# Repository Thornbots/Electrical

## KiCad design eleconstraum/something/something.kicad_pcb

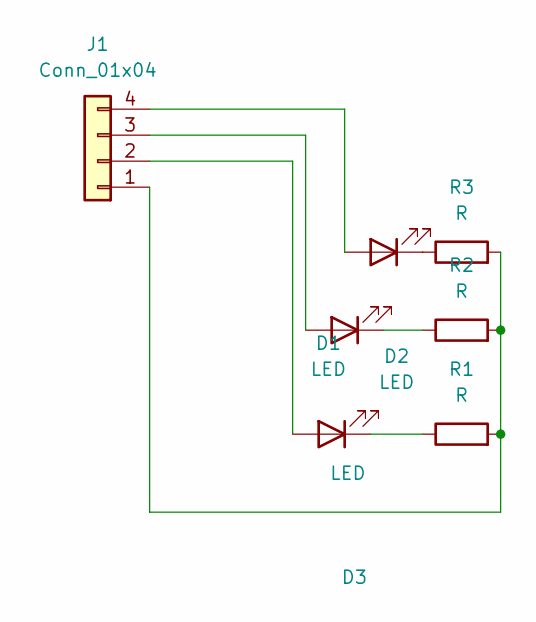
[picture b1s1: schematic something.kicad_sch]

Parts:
D1, D2, D3: LED
J1: Conn_01x04
R1, R2, R3: R

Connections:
unnamed: D1.2 (A), J1.4
unnamed: D1.1 (K), R3.1
unnamed: D2.2 (A), J1.3
unnamed: D2.1 (K), R2.1
unnamed: D3.2 (A), J1.2
unnamed: D3.1 (K), R1.1
unnamed: J1.1, R1.2, R2.2, R3.2

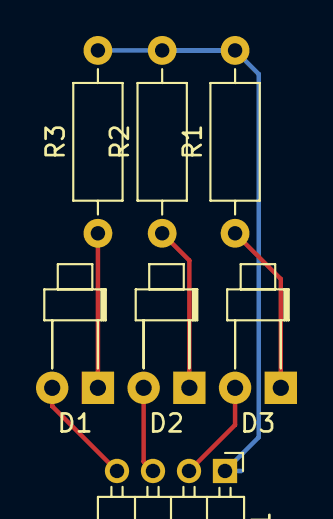
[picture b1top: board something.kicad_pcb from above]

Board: 2 copper layers, 7 parts (0 on the bottom side), 7 nets.

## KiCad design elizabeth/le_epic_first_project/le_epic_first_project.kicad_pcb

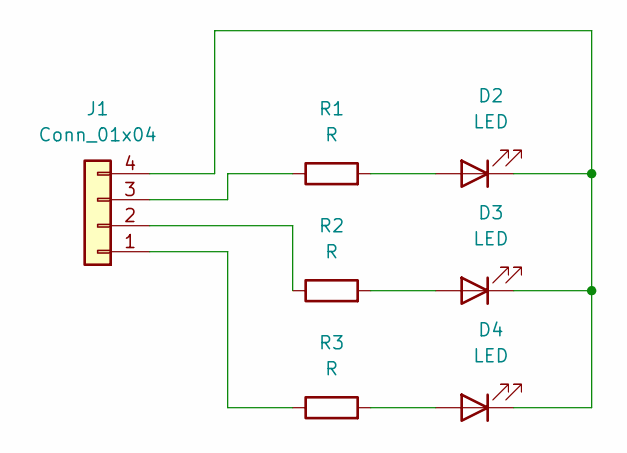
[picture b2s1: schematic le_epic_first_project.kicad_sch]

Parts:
D2, D3, D4: LED
J1: Conn_01x04
R1, R2, R3: R

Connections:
unnamed: D2.2 (A), R1.2
unnamed: D2.1 (K), D3.1 (K), D4.1 (K), J1.4
unnamed: D3.2 (A), R2.2
unnamed: D4.2 (A), R3.2
unnamed: J1.1, R3.1
unnamed: J1.2, R2.1
unnamed: J1.3, R1.1

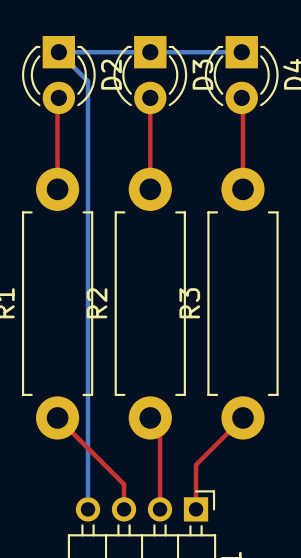
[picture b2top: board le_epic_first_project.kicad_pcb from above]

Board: 2 copper layers, 7 parts (0 on the bottom side), 7 nets.

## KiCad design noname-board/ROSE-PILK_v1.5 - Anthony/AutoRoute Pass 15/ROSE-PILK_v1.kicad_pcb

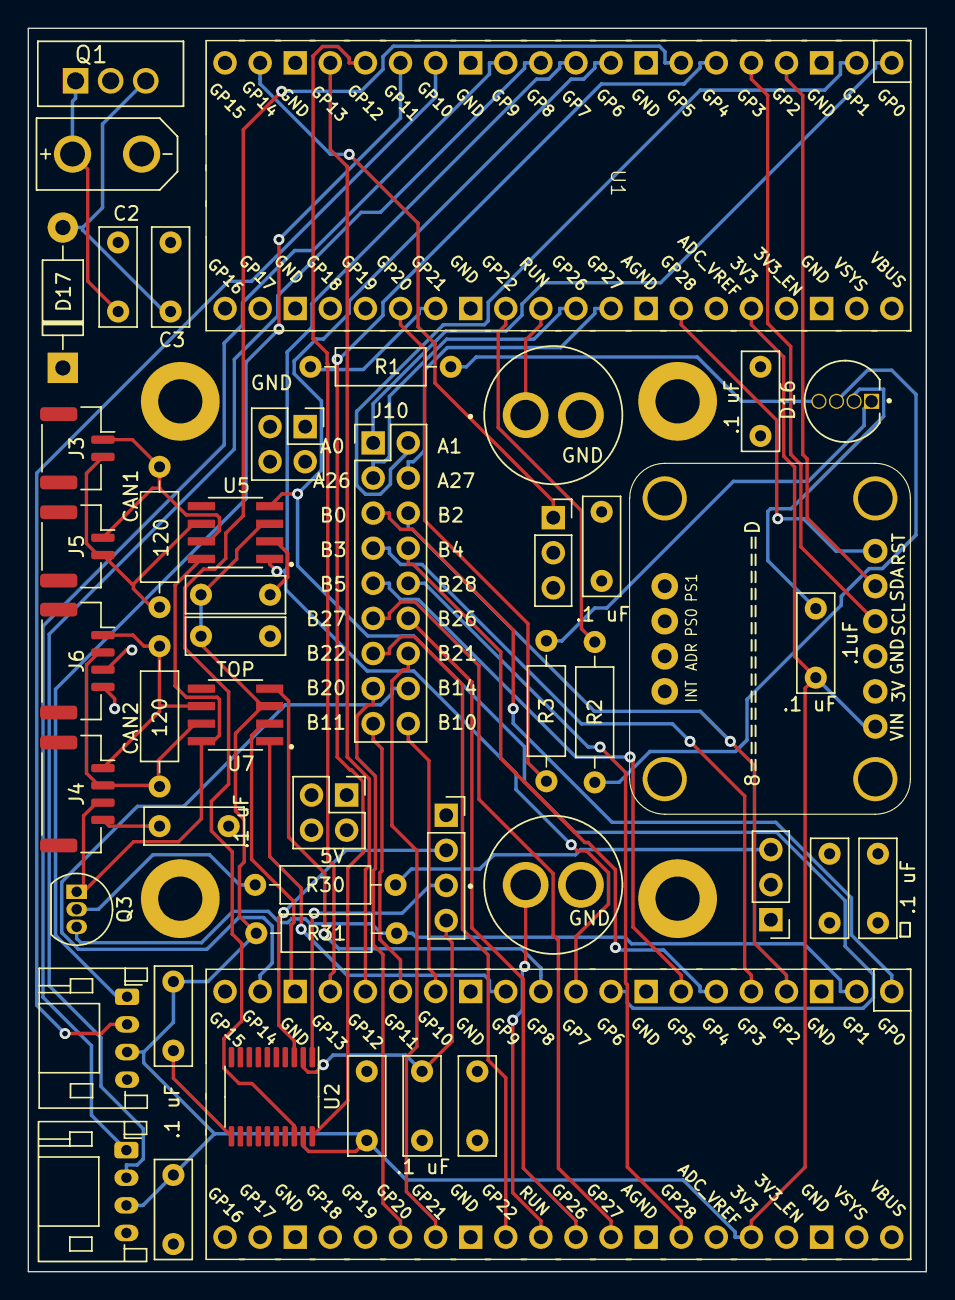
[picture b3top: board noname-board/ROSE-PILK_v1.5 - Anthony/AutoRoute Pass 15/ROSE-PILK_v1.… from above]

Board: 4 copper layers, 65.0 x 90.0 mm, 50 parts (0 on the bottom side), 57 nets.

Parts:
5VCAP1: .1uF; C_Disc_D7.0mm_W2.5mm_P5.00mm
C2: .47uF; C_Disc_D7.0mm_W2.5mm_P5.00mm
C3: 22uF; C_Disc_D7.0mm_W2.5mm_P5.00mm
CAN1, CAN2: .1uF; C_Disc_D7.0mm_W2.5mm_P5.00mm
D16: WP154A4SUREQBFZGC; LED_WP154A4SUREQBFZGC
D17: 1N5817; D_DO-41_SOD81_P10.16mm_Horizontal
DR16: .1uF; C_Disc_D7.0mm_W2.5mm_P5.00mm
IMU: BNO055
IMUC13: .1uF; C_Disc_D7.0mm_W2.5mm_P5.00mm
J1: Conn_01x04; PinSocket_1x04_P2.54mm_Vertical
J2: Conn_01x03; PinHeader_1x03_P2.54mm_Vertical
J3, J5: Conn_01x02; JST_GH_SM02B-GHS-TB_1x02-1MP_P1.25mm_Horizontal
J4, J6: Conn_01x04; JST_GH_SM04B-GHS-TB_1x04-1MP_P1.25mm_Horizontal
J7, J11: Conn_01x04; JST_PH_S4B-PH-K_1x04_P2.00mm_Horizontal
J10: Conn_02x09_Counter_Clockwise; PinHeader_2x09_P2.54mm_Vertical
J12, J13: Conn_02x02_Counter_Clockwise; PinSocket_2x02_P2.54mm_Vertical
JETSON1V8, JETSON3V3: .1uF; C_Disc_D7.0mm_W2.5mm_P5.00mm
JETSONGND1: .1uF; C_Disc_D7.0mm_W2.5mm_P5.00mm
Jw: Conn_01x03; PinSocket_1x03_P2.54mm_Vertical
MountingHole1, MountingHole2, MountingHole3: MountingHole_3.2mm_M3_ISO7380_Pad
PICOU1, PICOU6: .1uF; C_Disc_D7.0mm_W2.5mm_P5.00mm
Q1: LM2940CT-5.0_NOPB; TO254P1054X470X1955-3
Q3: PN2222A; TO-92_Inline
QUAD1, QUAD2: .1uF; C_Disc_D7.0mm_W2.5mm_P5.00mm
R1: 250; R_Axial_DIN0207_L6.3mm_D2.5mm_P10.16mm_Horizontal
R2: 220; R_Axial_DIN0207_L6.3mm_D2.5mm_P10.16mm_Horizontal
R3: 333; R_Axial_DIN0207_L6.3mm_D2.5mm_P10.16mm_Horizontal
R30, R31: R; R_Axial_DIN0207_L6.3mm_D2.5mm_P10.16mm_Horizontal
R32, R33: 120; R_Axial_DIN0207_L6.3mm_D2.5mm_P10.16mm_Horizontal
SERVO1: .1uF; C_Disc_D7.0mm_W2.5mm_P5.00mm
SW1, SW2: SW_Push; SW_PS1024ALRED
U1: Pico A; Updated_Pico
U2: TXS0108EPW; TSSOP-20_4.4x6.5mm_P0.65mm
U4: XT30UPB-M
U5, U7: SN65HVD230DR; SOIC127P599X175-8N
U6: Pico B; Updated_Pico

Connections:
/3V3: CAN1.1, CAN2.1, IMU.1, IMUC13.1, J7.3, J11.3, JETSON3V3.1, QUAD1.1, QUAD2.1, R31.1, U1.36 (3V3), U2.19 (VCCB), U5.3 (VCC), U6.36 (3V3), U7.3 (VCC)
/5V: 5VCAP1.1, 5VCAP1.2, D17.1 (K), DR16.2, J2.2, J4.4, J6.4, J13.1, J13.2, J13.3, J13.4, Jw.2, PICOU1.1, PICOU6.1, SERVO1.2, U1.39 (VSYS), U6.39 (VSYS)
/A0: J10.1, U1.1 (GPIO0)
/A1: J10.2, U1.2 (GPIO1)
/A26: J10.3, U1.31 (GPIO26_ADC0)
/A27: J10.4, U1.32 (GPIO27_ADC1)
/B0: J10.5, U6.1 (GPIO0)
/B2: J10.6, U6.4 (GPIO2)
/B3: J10.7, U6.5 (GPIO3)
/B4: J10.8, U6.6 (GPIO4)
/B5: J10.9, U6.7 (GPIO5)
/B10: J10.18, U6.14 (GPIO10)
/B11: J10.17, U6.15 (GPIO11)
/B14: J10.16, U6.19 (GPIO14)
/B20: J10.15, U6.26 (GPIO20)
/B21: J10.14, U6.27 (GPIO21)
/B22: J10.13, U6.29 (GPIO22)
/B26: J10.12, U6.31 (GPIO26_ADC0)
/B27: J10.11, U6.32 (GPIO27_ADC1)
/B28: J10.10, U6.34 (GPIO28_ADC2)
/CAN1_RX: U1.9 (GPIO6), U5.4 (R), U6.9 (GPIO6)
/CAN1_TX: U1.10 (GPIO7), U5.1 (D), U6.10 (GPIO7)
/CAN2_RX: U6.11 (GPIO8), U7.4 (R)
/CAN2_TX: U6.12 (GPIO9), U7.1 (D)
/DR16_TX: Q3.3 (C), R31.2, U6.2 (GPIO1)
/GND: C2.2, C3.2, CAN1.2, CAN2.2, D16.2, DR16.1, IMU.3, IMUC13.2, J1.1, J2.1, J4.3, J6.3, J7.4, J11.4, J12.1, J12.2, J12.3, J12.4, JETSON1V8.1, JETSON3V3.2, JETSONGND1.1, JETSONGND1.2, Jw.3, PICOU1.2, PICOU6.2, Q1.2 (GND), Q3.1 (E), QUAD1.2, QUAD2.2, SERVO1.1, SW1.2, SW2.2, U1.3 (GND), U1.8 (GND), U1.13 (GND), U1.18 (GND), U1.23 (GND), U1.28 (GND), U1.33 (AGND), U1.38 (GND), U2.11 (GND), U4.P$2 (-), U5.2 (GND), U5.8 (RS), U6.3 (GND), U6.8 (GND), U6.13 (GND), U6.18 (GND), U6.23 (GND), U6.28 (GND), U6.33 (AGND), U6.38 (GND), U7.2 (GND), U7.8 (RS)
/IMU_RST: IMU.6, U1.34 (GPIO28_ADC2)
/IMU_SCL: IMU.4, U1.5 (GPIO3)
/IMU_SDA: IMU.5, U1.4 (GPIO2)
/JETSON_rx: U1.6 (GPIO4), U2.20 (B1)
/JETSON_tx: U1.7 (GPIO5), U2.18 (B2)
/LEDB: R2.1, U1.29 (GPIO22)
/LEDG: R1.1, U1.27 (GPIO21)
/LEDR: R3.1, U1.26 (GPIO20)
/P2P_1: U1.16 (GPIO12), U6.17 (GPIO13)
/P2P_2: U1.17 (GPIO13), U6.16 (GPIO12)
/QUADA1: J7.2, U1.11 (GPIO8)
/QUADA2: J11.2, U1.14 (GPIO10)
/QUADB1: J7.1, U1.12 (GPIO9)
/QUADB2: J11.1, U1.15 (GPIO11)
/SERVO: Jw.1, U1.19 (GPIO14)
unnamed: D16.1, R3.2
unnamed: D16.3, R2.2
unnamed: D16.4, R1.2
unnamed: C3.1, D17.2 (A), Q1.3 (OUT)
unnamed: J1.2, U2.3 (A2)
unnamed: J1.3, U2.1 (A1)
unnamed: J1.4, JETSON1V8.2, U2.2 (VCCA)
unnamed: J2.3, R30.1
unnamed: J3.1, J5.1, R32.1, U5.7 (CANH)
unnamed: J3.2, J5.2, R32.2, U5.6 (CANL)
unnamed: J4.1, J6.1, R33.2, U7.6 (CANL)
unnamed: J4.2, J6.2, R33.1, U7.7 (CANH)
unnamed: C2.1, Q1.1 (IN), U4.P$1 (+)
unnamed: Q3.2 (B), R30.2
unnamed: SW1.1, U1.30 (RUN)
unnamed: SW2.1, U6.30 (RUN)

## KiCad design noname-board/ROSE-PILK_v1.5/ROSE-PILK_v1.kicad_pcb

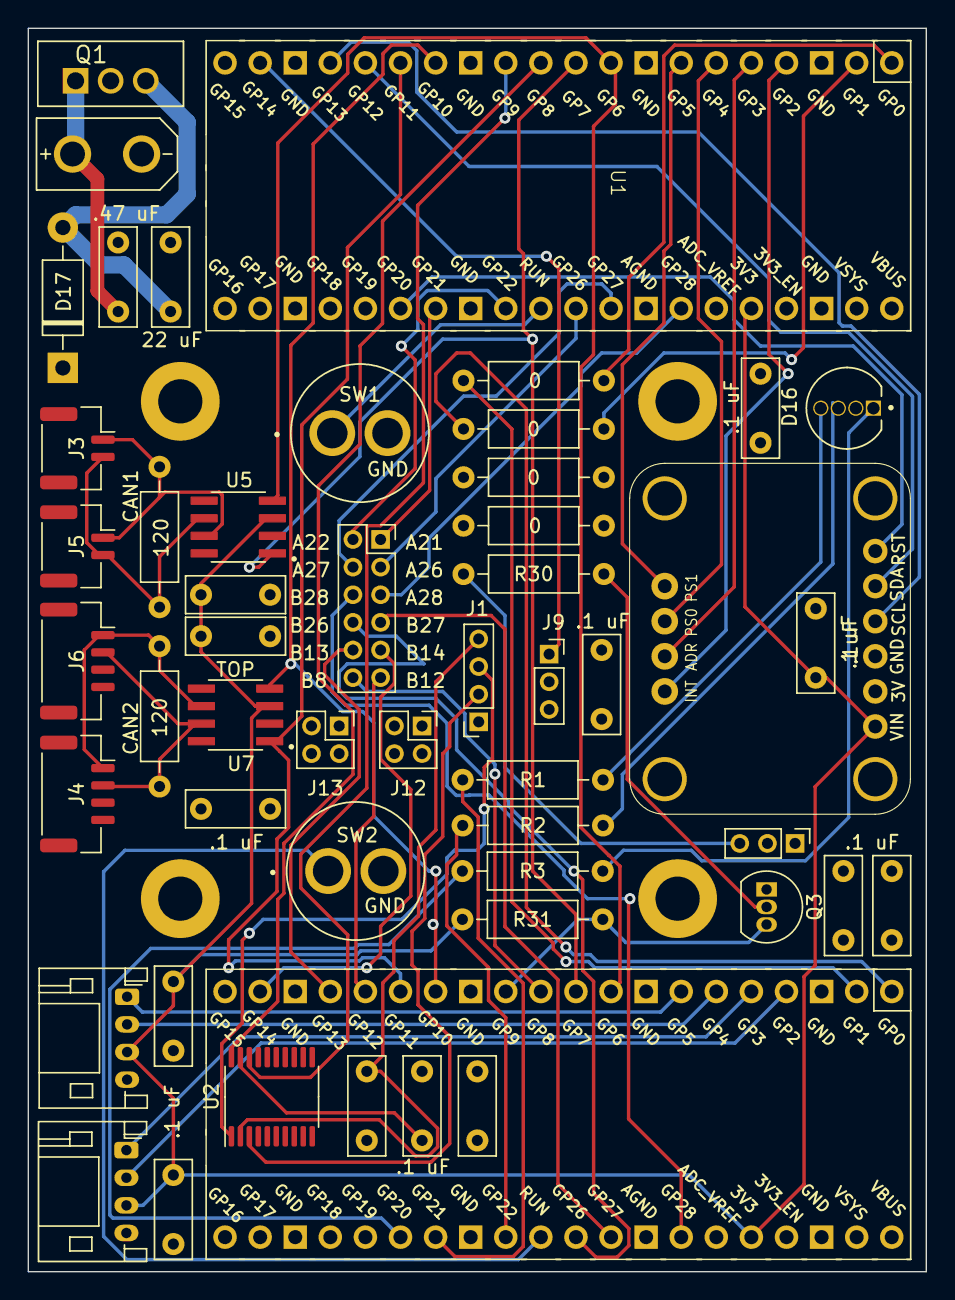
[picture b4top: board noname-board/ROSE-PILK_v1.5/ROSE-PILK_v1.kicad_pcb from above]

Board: 4 copper layers, 65.0 x 90.0 mm, 54 parts (0 on the bottom side), 59 nets.

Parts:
5VCAP1: .1uF; C_Disc_D7.0mm_W2.5mm_P5.00mm
22 uF: 22uF; C_Disc_D7.0mm_W2.5mm_P5.00mm
.47 uF: .47uF; C_Disc_D7.0mm_W2.5mm_P5.00mm
CAN1, CAN2: .1uF; C_Disc_D7.0mm_W2.5mm_P5.00mm
D16: WP154A4SUREQBFZGC; LED_WP154A4SUREQBFZGC
D17: 1N5817; D_DO-41_SOD81_P10.16mm_Horizontal
DR16: .1uF; C_Disc_D7.0mm_W2.5mm_P5.00mm
IMU: BNO055
IMUCAP: .1uF; C_Disc_D7.0mm_W2.5mm_P5.00mm
J1: Conn_01x04; PinSocket_1x04_P2.00mm_Vertical
J2: Conn_01x03; PinHeader_1x03_P2.00mm_Vertical
J3, J5: Conn_01x02; JST_GH_SM02B-GHS-TB_1x02-1MP_P1.25mm_Horizontal
J4, J6: Conn_01x04; JST_GH_SM04B-GHS-TB_1x04-1MP_P1.25mm_Horizontal
J7, J11: Conn_01x04; JST_PH_S4B-PH-K_1x04_P2.00mm_Horizontal
J8: Conn_02x06_Counter_Clockwise; PinSocket_2x06_P2.00mm_Vertical
J9: Conn_01x03; PinSocket_1x03_P2.00mm_Vertical
J12, J13: Conn_02x02_Counter_Clockwise; PinSocket_2x02_P2.00mm_Vertical
JETSON1V8, JETSON3V3: .1uF; C_Disc_D7.0mm_W2.5mm_P5.00mm
JETSONGND1: .1uF; C_Disc_D7.0mm_W2.5mm_P5.00mm
MountingHole1, MountingHole2, MountingHole3: MountingHole_3.2mm_M3_ISO7380_Pad
PICOU1, PICOU6: .1uF; C_Disc_D7.0mm_W2.5mm_P5.00mm
Q1: LM2940CT-5.0_NOPB; TO254P1054X470X1955-3
Q3: PN2222A; TO-92_Inline
QUAD1, QUAD2: .1uF; C_Disc_D7.0mm_W2.5mm_P5.00mm
R1: 250; R_Axial_DIN0207_L6.3mm_D2.5mm_P10.16mm_Horizontal
R2: 220; R_Axial_DIN0207_L6.3mm_D2.5mm_P10.16mm_Horizontal
R3: 333; R_Axial_DIN0207_L6.3mm_D2.5mm_P10.16mm_Horizontal
R4, R5, R10, R20: 0; R_Axial_DIN0207_L6.3mm_D2.5mm_P10.16mm_Horizontal
R30, R31: R; R_Axial_DIN0207_L6.3mm_D2.5mm_P10.16mm_Horizontal
R32, R33: 120; R_Axial_DIN0207_L6.3mm_D2.5mm_P10.16mm_Horizontal
SERVO1: .1uF; C_Disc_D7.0mm_W2.5mm_P5.00mm
SW1, SW2: SW_Push; SW_PS1024ALRED
U1, U6: Pico; Updated_Pico
U2: TXS0108EPW; TSSOP-20_4.4x6.5mm_P0.65mm
U4: XT30UPB-M
U5, U7: SN65HVD230DR; SOIC127P599X175-8N

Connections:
/3V3: CAN1.1, CAN2.1, IMU.1, IMUCAP.1, J7.3, J11.3, QUAD1.1, QUAD2.1, R31.1, U1.36 (3V3), U5.3 (VCC), U6.36 (3V3), U7.3 (VCC)
/5V: 5VCAP1.1, 5VCAP1.2, D17.1 (K), DR16.2, J2.2, J4.4, J6.4, J9.2, J13.1, J13.2, J13.3, J13.4, PICOU1.1, PICOU6.1, SERVO1.2, U1.39 (VSYS), U6.39 (VSYS)
/A21: J8.1, U1.27 (GPIO21)
/A22: J8.2, U1.29 (GPIO22)
/A26: J8.3, U1.31 (GPIO26_ADC0)
/A27: J8.4, U1.32 (GPIO27_ADC1)
/A28: J8.5, U1.34 (GPIO28_ADC2)
/ADR: IMU.2, U1.5 (GPIO3)
/B8: J8.12, U6.11 (GPIO8)
/B12: J8.11, U6.16 (GPIO12)
/B13: J8.10, U6.17 (GPIO13)
/B14: J8.9, U6.19 (GPIO14)
/B26: J8.8, U6.31 (GPIO26_ADC0)
/B27: J8.7, U6.32 (GPIO27_ADC1)
/B28: J8.6, U6.34 (GPIO28_ADC2)
/CAN1_RX: U1.9 (GPIO6), U5.4 (R), U6.9 (GPIO6)
/CAN1_TX: U1.10 (GPIO7), U5.1 (D), U6.10 (GPIO7)
/CAN2_RX: U1.14 (GPIO10), U6.14 (GPIO10), U7.4 (R)
/CAN2_TX: U1.15 (GPIO11), U6.15 (GPIO11), U7.1 (D)
/DR16-TX: Q3.3 (C), R31.2, U6.12 (GPIO9)
/GND: 22 uF.2, .47 uF.2, CAN1.2, CAN2.2, D16.2, DR16.1, IMU.3, IMUCAP.2, J2.1, J4.3, J6.3, J7.4, J9.3, J11.4, J12.1, J12.2, J12.3, J12.4, PICOU1.2, PICOU6.2, Q1.2 (GND), Q3.1 (E), QUAD1.2, QUAD2.2, SERVO1.1, SW1.2, SW2.2, U1.3 (GND), U1.8 (GND), U1.13 (GND), U1.18 (GND), U1.23 (GND), U1.28 (GND), U1.33 (AGND), U1.38 (GND), U4.P$2 (-), U5.2 (GND), U5.8 (RS), U6.3 (GND), U6.8 (GND), U6.13 (GND), U6.18 (GND), U6.23 (GND), U6.28 (GND), U6.33 (AGND), U6.38 (GND), U7.2 (GND), U7.8 (RS)
/GPIO0-A: R4.1, U6.1 (GPIO0)
/GPIO0-B: R5.2, U1.1 (GPIO0)
/GPIO1-A: R5.1, U6.2 (GPIO1)
/GPIO1-B: R4.2, U1.2 (GPIO1)
/IMU_RST: IMU.6, U1.26 (GPIO20)
/IMU_SCL: IMU.4, U1.17 (GPIO13)
/IMU_SDA: IMU.5, U1.16 (GPIO12)
/INT: IMU.1, U1.4 (GPIO2)
/JETSON_UART/3V3: JETSON3V3.1, U2.19 (VCCB)
/JETSON_UART/GND: J1.1, JETSON1V8.1, JETSON3V3.2, JETSONGND1.1, JETSONGND1.2, U2.11 (GND)
/JETSON_rx: U1.11 (GPIO8), U2.20 (B1)
/JETSON_tx: U1.12 (GPIO9), U2.18 (B2)
/LEDB: R2.1, U6.29 (GPIO22)
/LEDG: R1.1, U6.27 (GPIO21)
/LEDR: R3.1, U6.26 (GPIO20)
/PS0: IMU.3, U1.6 (GPIO4)
/PS1: IMU.4, U1.7 (GPIO5)
/QUADA1: J7.2, U6.4 (GPIO2)
/QUADA2: J11.2, U6.6 (GPIO4)
/QUADB1: J7.1, U6.5 (GPIO3)
/QUADB2: J11.1, U6.7 (GPIO5)
/SERVO: J9.1, U1.19 (GPIO14)
unnamed: D16.1, R3.2
unnamed: D16.3, R2.2
unnamed: D16.4, R1.2
unnamed: 22 uF.1, D17.2 (A), Q1.3 (OUT)
unnamed: J1.2, U2.3 (A2)
unnamed: J1.3, U2.1 (A1)
unnamed: J1.4, JETSON1V8.2, U2.2 (VCCA)
unnamed: J2.3, R30.1
unnamed: J3.1, J5.1, R32.1, U5.7 (CANH)
unnamed: J3.2, J5.2, R32.2, U5.6 (CANL)
unnamed: J4.1, J6.1, R33.2, U7.6 (CANL)
unnamed: J4.2, J6.2, R33.1, U7.7 (CANH)
unnamed: .47 uF.1, Q1.1 (IN), U4.P$1 (+)
unnamed: Q3.2 (B), R30.2
unnamed: SW1.1, U1.30 (RUN)
unnamed: SW2.1, U6.30 (RUN)

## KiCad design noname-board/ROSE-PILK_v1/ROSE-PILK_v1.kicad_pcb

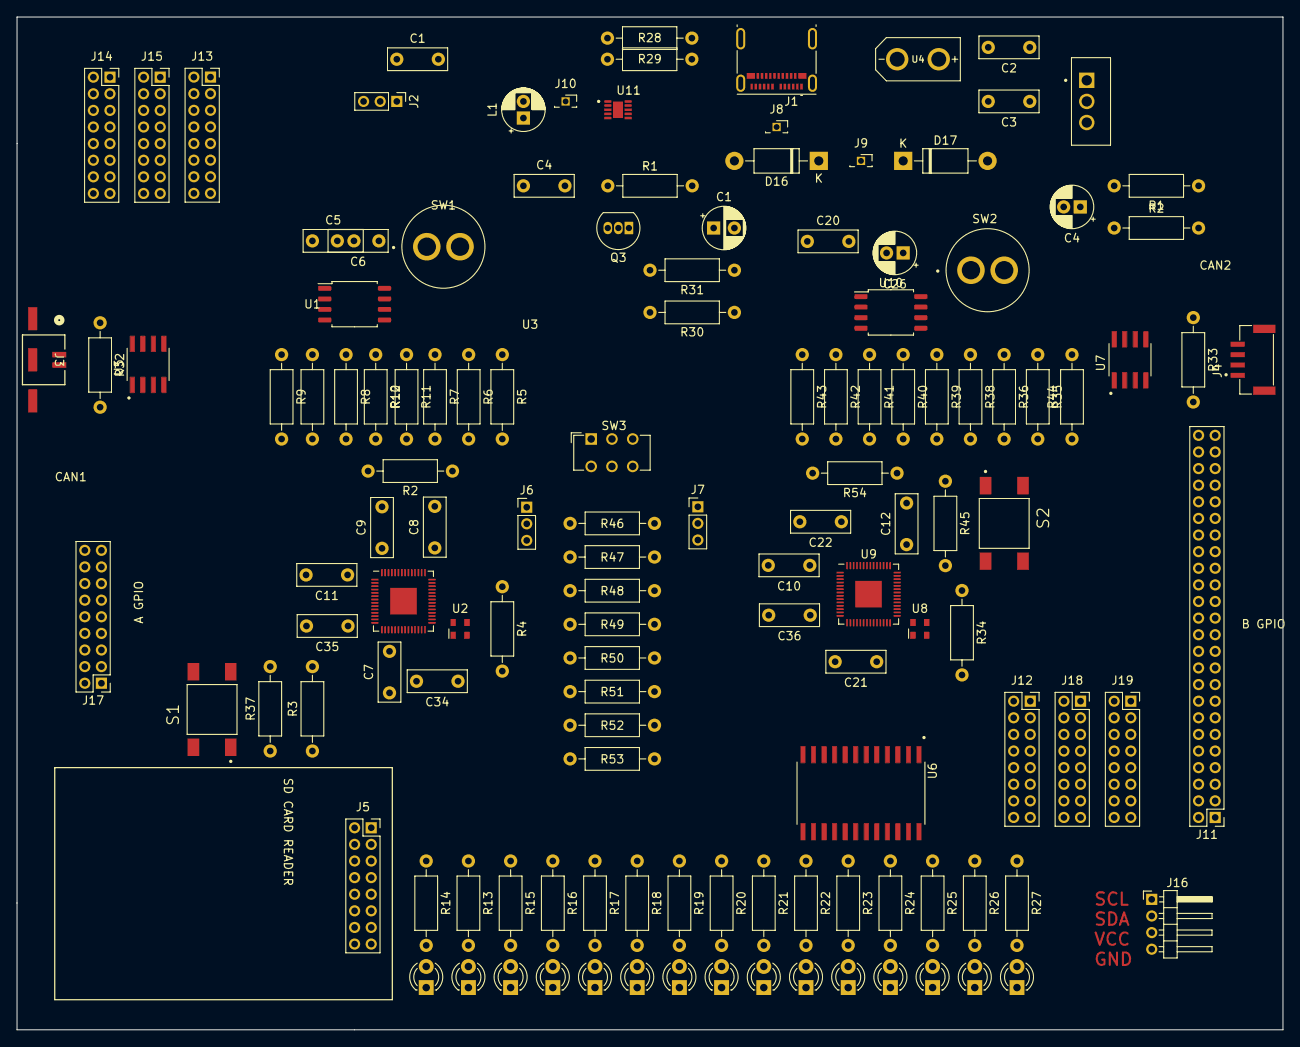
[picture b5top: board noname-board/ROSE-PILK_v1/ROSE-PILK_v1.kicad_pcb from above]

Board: 6 copper layers, 152.4 x 121.9 mm, 132 parts (0 on the bottom side), 155 nets, no tracks yet.

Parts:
C1, C4: 47uF; C_Disc_D7.0mm_W2.5mm_P5.00mm
C1#2: 10uF; CP_Radial_D5.0mm_P2.50mm
C2: .47uF; C_Disc_D7.0mm_W2.5mm_P5.00mm
C3: 22uF; C_Disc_D7.0mm_W2.5mm_P5.00mm
C4#2: 10uF MUST BE TANTALUM; CP_Radial_D5.0mm_P2.00mm
C5, C6, C7, C8, C9, C10, C11, C12, C20, C21, C22, C34, C35, C36: 1uF; C_Disc_D7.0mm_W2.5mm_P5.00mm
C26: 1uF; CP_Radial_D5.0mm_P2.00mm
D1, D2, D3, D4, D5, D6, D7, D8, D9, D10, D11, D12, D13, D14, D15: LED; LED_D3.0mm
D16, D17: 1N5817; D_DO-41_SOD81_P10.16mm_Horizontal
J1: USB_C_Receptacle; USB_C_Receptacle_Molex_105450-0101
J2, J6, J7: Conn_01x03; PinHeader_1x03_P2.00mm_Vertical
J3: Conn_01x02; CONN_SM02B-GHS-TB_JST
J4: Conn_01x04; JST_SM04B-GHS-TB_LF__SN_-
J5: Conn_02x08_Odd_Even; PinSocket_2x08_P2.00mm_Vertical
J8, J9, J10: Conn_01x01_Pin; PinSocket_1x01_P1.27mm_Vertical
J11: Conn_02x24_Odd_Even; PinHeader_2x24_P2.00mm_Vertical
J12, J13, J14, J15, J18, J19: Conn_02x08_Counter_Clockwise; PinSocket_2x08_P2.00mm_Vertical
J16: Conn_01x04_Pin; PinHeader_1x04_P2.00mm_Horizontal
J17: Conn_02x09_Odd_Even; PinHeader_2x09_P2.00mm_Vertical
L1: 2.2uH; CP_Radial_D5.0mm_P2.00mm
Q1: LM2940CT-5.0_NOPB; TO254P1054X470X1955-3
Q3: PN2222A; TO-92_Inline
R1: 100K; R_Axial_DIN0207_L6.3mm_D2.5mm_P10.16mm_Horizontal
R1#2: 5k; R_Axial_DIN0207_L6.3mm_D2.5mm_P10.16mm_Horizontal
R2: 121 Nominal; R_Axial_DIN0207_L6.3mm_D2.5mm_P10.16mm_Horizontal
R2#2, R54: 200; R_Axial_DIN0207_L6.3mm_D2.5mm_P10.16mm_Horizontal
R3, R4, R5, R34, R35, R44: 10K; R_Axial_DIN0207_L6.3mm_D2.5mm_P10.16mm_Horizontal
R6, R7, R8, R9, R10, R11, R12, R36, R38, R39, R40, R41, R42, R43: 27; R_Axial_DIN0207_L6.3mm_D2.5mm_P10.16mm_Horizontal
R13, R14, R15, R16, R17, R18, R19, R20, R21, R22, R23, R24, R25, R26, R27: R_US; R_Axial_DIN0207_L6.3mm_D2.5mm_P10.16mm_Horizontal
R28, R29: 5.1K; R_Axial_DIN0207_L6.3mm_D2.5mm_P10.16mm_Horizontal
R30, R31: R; R_Axial_DIN0207_L6.3mm_D2.5mm_P10.16mm_Horizontal
R32, R33: 120; R_Axial_DIN0207_L6.3mm_D2.5mm_P10.16mm_Horizontal
R37, R45: 1K; R_Axial_DIN0207_L6.3mm_D2.5mm_P10.16mm_Horizontal
R46, R47, R48, R49, R50, R51, R52, R53: 0; R_Axial_DIN0207_L6.3mm_D2.5mm_P10.16mm_Horizontal
S1, S2: TL3301NF160QG; SW_TL3301NF160QG
SW1, SW2: SW_Push; SW_PS1024ALRED
SW3: SW_Push_DPDT; SW_CuK_JS202011CQN_DPDT_Straight
U1, U10: W25Q128JVS; SOIC-8_5.23x5.23mm_P1.27mm
U2, U8: ASDMB-12MHz; Oscillator_SMD_Abracon_ASDMB-4Pin_2.5x2.0mm
U3, U9: RP2040; QFN-56-1EP_7x7mm_P0.4mm_EP3.2x3.2mm
U4: XT30UPB-M
U5, U7: SN65HVD230DR; SOIC127P599X175-8N
U6: CD4514BM; SOIC127P1030X265-24N
U11: RT6150B-33GQW; SON50P250X250X80-11N

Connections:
/1V1: C8.1, C22.1, U3.23 (DVDD), U3.45 (VREG_VOUT), U3.50 (DVDD), U9.23 (DVDD), U9.45 (VREG_VOUT), U9.50 (DVDD)
/3V3: C4.1, C4#2.1, C5.2, C7.1, C9.1, C10.1, C21.1, C26.1, C34.2, C35.1, C36.1, J5.3, J5.4, J15.1, J15.2, J15.3, J15.4, J15.5, J15.6, J15.7, J15.8, J15.9, J15.10, J15.11, J15.12, J15.13, J15.14, J15.15, J15.16, J18.1, J18.2, J18.3, J18.4, J18.5, J18.6, J18.7, J18.8, J18.9, J18.10, J18.11, J18.12, J18.13, J18.14, J18.15, J18.16, R2.1, R2#2.2, R3.2, R4.1, R5.1, R31.1, R34.1, R35.1, R44.2, R54.2, U1.8 (VCC), U2.4 (VDD), U3.1 (IOVDD), U3.10 (IOVDD), U3.22 (IOVDD), U3.33 (IOVDD), U3.42 (IOVDD), U3.44 (VREG_IN), U3.48 (USB_VDD), U3.49 (IOVDD), U5.3 (VCC), U7.3 (VCC), U8.4 (VDD), U9.1 (IOVDD), U9.10 (IOVDD), U9.22 (IOVDD), U9.33 (IOVDD), U9.42 (IOVDD), U9.44 (VREG_IN), U9.48 (USB_VDD), U9.49 (IOVDD), U10.8 (VCC), U11.1 (VOUT), U11.10 (FB)
/5V: C1.1, D16.1 (K), D17.1 (K), J2.2, J4.4, J5.5, J5.6, J9.1, J12.1, J12.2, J12.3, J12.4, J12.5, J12.6, J12.7, J12.8, J12.9, J12.10, J12.11, J12.12, J12.13, J12.14, J12.15, J12.16, J14.1, J14.2, J14.3, J14.4, J14.5, J14.6, J14.7, J14.8, J14.9, J14.10, J14.11, J14.12, J14.13, J14.14, J14.15, J14.16, J16.3, R1.1, U6.24 (VDD), U11.5 (VIN), U11.8 (VINA)
/A8: J17.1, J17.2, U3.11 (GPIO8)
/A9: J17.3, J17.4, U3.12 (GPIO9)
/A10: J17.5, J17.6, U3.13 (GPIO10)
/A11: J17.7, J17.8, U3.14 (GPIO11)
/A12: J17.9, J17.10, U3.34 (GPIO22)
/A26: J17.11, J17.12, U3.38 (GPIO26_ADC0)
/A27: J17.13, J17.14, U3.39 (GPIO27_ADC1)
/A28: J17.15, J17.16, U3.40 (GPIO28_ADC2)
/A29: J17.17, J17.18, U3.41 (GPIO29_ADC3)
/A-D+: R7.2, SW3.1 (A)
/A-D-: R6.1, SW3.4 (A)
/B6: J11.1, J11.2, U9.8 (GPIO6)
/B7: J11.3, J11.4, U9.9 (GPIO7)
/B8: J11.5, J11.6, U9.11 (GPIO8)
/B9: J11.7, J11.8, U9.12 (GPIO9)
/B10: J11.9, J11.10, U9.13 (GPIO10)
/B11: J11.11, J11.12, U9.14 (GPIO11)
/B12: J11.13, J11.14, U9.15 (GPIO12)
/B13: J11.15, J11.16, U9.16 (GPIO13)
/B14: J11.17, J11.18, U9.17 (GPIO14)
/B15: J11.19, J11.20, U9.18 (GPIO15)
/B16: J11.21, J11.22, U9.27 (GPIO16)
/B17: J11.23, J11.24, U9.28 (GPIO17)
/B18: J11.25, J11.26, U9.29 (GPIO18)
/B19: J11.27, J11.28, U9.30 (GPIO19)
/B20: J11.29, J11.30, U9.31 (GPIO20)
/B21: J11.31, J11.32, U9.32 (GPIO21)
/B22: J11.33, J11.34, U9.34 (GPIO22)
/B23: J11.35, J11.36, U9.35 (GPIO23)
/B24: J11.37, J11.38, U9.36 (GPIO24)
/B25: J11.39, J11.40, U9.37 (GPIO25)
/B26: J11.41, J11.42, U9.38 (GPIO26_ADC0)
/B27: J11.43, J11.44, U9.39 (GPIO27_ADC1)
/B28: J11.45, J11.46, U9.40 (GPIO28_ADC2)
/B29: J11.47, J11.48, U9.41 (GPIO29_ADC3)
/B-D+: R38.2, SW3.3 (C)
/B-D-: R36.1, SW3.6 (C)
/BOOTSEL1/QSPI_SS: R44.1, R45.2, U9.56 (QSPI_SS), U10.1 (~CS)
/BOOTSEL/QSPI_SS: R3.1, R37.2, U1.1 (~CS), U3.56 (QSPI_SS)
/CAN1_RX: U3.17 (GPIO14), U5.4 (R)
/CAN1_TX: U3.18 (GPIO15), U5.1 (D)
/CAN2_RX: U3.27 (GPIO16), U7.4 (R)
/CAN2_TX: U3.28 (GPIO17), U7.1 (D)
/CS: J5.7, J5.8, U3.35 (GPIO23)
/DR16-RX: Q3.3 (C), R31.2, U3.16 (GPIO13)
/Flash Memory1/CLK: R43.1, U10.6 (CLK)
/Flash Memory1/IO0: R39.1, U10.5 (DI(IO0))
/Flash Memory1/IO1: R40.1, U10.2 (DO(IO1))
/Flash Memory1/IO2: R41.1, U10.3 (IO2)
/Flash Memory1/IO3: R42.1, U10.7 (IO3)
/Flash Memory/CLK: R12.1, U1.6 (CLK)
/Flash Memory/IO0: R8.1, U1.5 (DI(IO0))
/Flash Memory/IO1: R9.1, U1.2 (DO(IO1))
/Flash Memory/IO2: R10.1, U1.3 (IO2)
/Flash Memory/IO3: R11.1, U1.7 (IO3)
/GND: C1.2, C1#2.2, C2.2, C3.2, C4.2, C4#2.2, C5.1, C6.2, C7.2, C8.2, C9.2, C10.2, C11.2, C12.2, C20.2, C21.2, C22.2, C26.2, C34.1, C35.2, C36.2, D1.1 (K), D2.1 (K), D3.1 (K), D4.1 (K), D5.1 (K), D6.1 (K), D7.1 (K), D8.1 (K), D9.1 (K), D10.1 (K), D11.1 (K), D12.1 (K), D13.1 (K), D14.1 (K), D15.1 (K), J1.A1 (GND), J1.A12 (GND), J1.B1 (GND), J1.B12 (GND), J1.S1 (SHIELD), J2.1, J4.3, J5.1, J5.2, J5.15, J5.16, J6.2, J7.2, J10.1, J13.1, J13.2, J13.3, J13.4, J13.5, J13.6, J13.7, J13.8, J13.9, J13.10, J13.11, J13.12, J13.13, J13.14, J13.15, J13.16, J16.4, J19.1, J19.2, J19.3, J19.4, J19.5, J19.6, J19.7, J19.8, J19.9, J19.10, J19.11, J19.12, J19.13, J19.14, J19.15, J19.16, Q1.2 (GND), Q3.1 (E), R1#2.2, R28.2, R29.2, S1.2, S1.4, S2.2, S2.4, SW1.2, SW2.2, U1.4 (GND), U2.2 (GND), U3.19 (TESTEN), U3.57 (GND), U4.P$2 (-), U5.2 (GND), U5.8 (RS), U6.12 (VSS), U7.2 (GND), U7.8 (RS), U8.2 (GND), U9.19 (TESTEN), U9.57 (GND), U10.4 (GND), U11.3 (GND), U11.7 (PS), U11.9 (GND__1), U11.11 (EXP)
/GPIO0-A: R53.2, U3.2 (GPIO0)
/GPIO0-B: R49.2, U9.2 (GPIO0)
/GPIO1-A: R52.2, U3.3 (GPIO1)
/GPIO1-B: R48.2, U9.3 (GPIO1)
/GPIO2-A: R46.1, U3.4 (GPIO2)
/GPIO2-B: R50.1, U9.4 (GPIO2)
/GPIO3-A: R47.1, U3.5 (GPIO3)
/GPIO3-B: R51.1, U9.5 (GPIO3)
/GPIO4-A: R48.1, U3.6 (GPIO4)
/GPIO4-B: R52.1, U9.6 (GPIO4)
/GPIO5-A: R49.1, U3.7 (GPIO5)
/GPIO5-B: R53.1, U9.7 (GPIO5)
/LED Arrray/LEDx15/out_pin 1: R13.1, U6.10 (S1)
/LED Arrray/LEDx15/out_pin 2: R14.1, U6.9 (S2)
/LED Arrray/LEDx15/out_pin 3: R15.1, U6.8 (S3)
/LED Arrray/LEDx15/out_pin 4: R16.1, U6.7 (S4)
/LED Arrray/LEDx15/out_pin 5: R17.1, U6.6 (S5)
/LED Arrray/LEDx15/out_pin 6: R18.1, U6.5 (S6)
/LED Arrray/LEDx15/out_pin 7: R19.1, U6.4 (S7)
/LED Arrray/LEDx15/out_pin 8: R20.1, U6.18 (S8)
/LED Arrray/LEDx15/out_pin 9: R21.1, U6.17 (S9)
/LED Arrray/LEDx15/out_pin 10: R22.1, U6.20 (S10)
/LED Arrray/LEDx15/out_pin 11: R23.1, U6.19 (S11)
/LED Arrray/LEDx15/out_pin 12: R24.1, U6.14 (S12)
/LED Arrray/LEDx15/out_pin 13: R25.1, U6.13 (S13)
/LED Arrray/LEDx15/out_pin 14: R26.1, U6.16 (S14)
/LED Arrray/LEDx15/out_pin 15: R27.1, U6.15 (S15)
/LED Arrray/input 1: U3.32 (GPIO21), U6.2 (DATA1)
/LED Arrray/input 2: U3.31 (GPIO20), U6.3 (DATA2)
/LED Arrray/input 3: U3.30 (GPIO19), U6.21 (DATA3)
/LED Arrray/input 4: U3.29 (GPIO18), U6.22 (DATA4)
/MISO: J5.13, J5.14, U3.15 (GPIO12)
/MOSI: J5.9, J5.10, U3.36 (GPIO24)
/RP2040/N_USB_D+: R7.1, U3.46 (USB_DM)
/RP2040/N_USB_D-: R6.2, U3.47 (USB_DP)
/RP2040/~RST: C6.1, R5.2, SW1.1, U3.26 (RUN)
/RP2041/N_USB_D+: R38.1, U9.46 (USB_DM)
/RP2041/N_USB_D-: R36.2, U9.47 (USB_DP)
/RP2041/~RST: C20.1, R35.2, SW2.1, U9.26 (RUN)
/SCK: J5.11, J5.12, U3.37 (GPIO25)
/SCL: J16.1, U3.9 (GPIO7)
/SDA: J16.2, U3.8 (GPIO6)
/SWCLK-A: J6.1, R50.2, U3.24 (SWCLK)
/SWCLK-B: J7.1, R46.2, U9.24 (SWCLK)
/SWDIO-A: J6.3, R51.2, U3.25 (SWD)
/SWDIO-B: J7.3, R47.2, U9.25 (SWD)
/USBC/D+: J1.A6 (D+), J1.B6 (D+), SW3.2 (B)
/USBC/D-: J1.A7 (D-), J1.B7 (D-), SW3.5 (B)
/USB_5V: D16.2 (A), J1.A4 (VBUS), J1.A9 (VBUS), J1.B4 (VBUS), J1.B9 (VBUS), J8.1
unnamed: D1.2 (A), R13.2
unnamed: D2.2 (A), R14.2
unnamed: D3.2 (A), R15.2
unnamed: D4.2 (A), R16.2
unnamed: D5.2 (A), R17.2
unnamed: D6.2 (A), R18.2
unnamed: D7.2 (A), R19.2
unnamed: D8.2 (A), R20.2
unnamed: D9.2 (A), R21.2
unnamed: D10.2 (A), R22.2
unnamed: D11.2 (A), R23.2
unnamed: D12.2 (A), R24.2
unnamed: D13.2 (A), R25.2
unnamed: D14.2 (A), R26.2
unnamed: D15.2 (A), R27.2
unnamed: C3.1, D17.2 (A), Q1.3 (OUT)
unnamed: J1.A5 (CC1), R29.1
unnamed: J1.B5 (CC2), R28.1
unnamed: J2.3, R30.1
unnamed: J3.1, R32.1, U5.7 (CANH)
unnamed: J3.2, R32.2, U5.6 (CANL)
unnamed: J4.1, R33.2, U7.6 (CANL)
unnamed: J4.2, R33.1, U7.7 (CANH)
unnamed: R1#2.1, R2.2
unnamed: C2.1, Q1.1 (IN), U4.P$1 (+)
unnamed: Q3.2 (B), R30.2
unnamed: R37.1, S1.1, S1.3
unnamed: R45.1, S2.1, S2.3
unnamed: U2.3 (Out), U3.20 (XIN)
unnamed: R4.2, U2.1 (Standby)
unnamed: C11.1, R2#2.1, U3.43 (ADC_AVDD)
unnamed: R12.2, U3.52 (QSPI_SCLK)
unnamed: R8.2, U3.53 (QSPI_SD0)
unnamed: R9.2, U3.55 (QSPI_SD1)
unnamed: R10.2, U3.54 (QSPI_SD2)
unnamed: R11.2, U3.51 (QSPI_SD3)
unnamed: U8.3 (Out), U9.20 (XIN)
unnamed: R34.2, U8.1 (Standby)
unnamed: C12.1, R54.1, U9.43 (ADC_AVDD)
unnamed: R43.2, U9.52 (QSPI_SCLK)
unnamed: R39.2, U9.53 (QSPI_SD0)
unnamed: R40.2, U9.55 (QSPI_SD1)
unnamed: R41.2, U9.54 (QSPI_SD2)
unnamed: R42.2, U9.51 (QSPI_SD3)
unnamed: R1.2, U11.6 (EN)
unnamed: L1.1, U11.4 (LX1)
unnamed: L1.2, U11.2 (LX2)
